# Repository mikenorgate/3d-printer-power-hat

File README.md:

# 3D Printer HAT

This 3D printer HAT is a PCB that allows you to connect your Raspberry PI to your 3D printer. The HAT (Hardware Attached on Top) sits on top of the Raspberry PI, allowing it to be powered by the printer's power supply. It also includes relays that allow the printer to be remotely turned on and off, making it easy to control your printer from your computer or mobile device.

## Board Features

- Step Down Voltage Converter: Converts the voltage supplied by your printer power supply unit (PSU) down to the 5 volts required by the Raspberry PI. This is an important safety feature, as using a higher voltage than the Raspberry PI is designed for can damage the board.
- Reverse Polarity Protection: Protects your Raspberry PI from damage in the event that the wiring is incorrectly connected. This can happen if you accidentally connect the positive and negative wires to the wrong pins on the HAT or the Raspberry PI.
- Backpower Protection: Will stop providing power to your PI via the HAT if you power it from a USB connection
- Printer Power Switch: Allows the power to the printer's main board to be remotely turned on and off. This is useful if you want to be able to start and stop your printer from your computer or mobile device.
- Auxiliary Power Switch: Can be used to power on and off an additional device, such as lights. This is useful if you want to be able to control other aspects of your printer setup from your computer or mobile device.
- PWM Fan Connector: Allows you to connect a pulse width modulation (PWM) fan to help keep the Raspberry PI cool. PWM fans are controlled by a signal from the Raspberry PI, which allows you to adjust their speed and therefore the amount of cooling they provide.

## Hardware Connection

To connect the HAT to your Raspberry PI and printer, you will need to follow the wiring diagram provided in the repository. This diagram shows you which pins on the HAT and the Raspberry PI need to be connected, as well as which wires from the printer's power supply need to be connected.

## Software

The HAT is compatible with the Klipper/Moonraker and Octoprint, which are open-source firmware and control software for 3D printers. Instructions for configuring these programs to work with the HAT are provided below.

### Klipper/Moonraker

To use the HAT with Klipper/Moonraker, you will need to add the following power configuration to your moonraker.conf file:

```yaml
[power printer]
type: gpio
pin: !gpiochip0/gpio17
initial_state: on
off_when_shutdown: True
off_when_shutdown_delay: 0
on_when_job_queued: True
locked_while_printing: True
restart_klipper_when_powered: True
restart_delay: 1.

[power aux]
type: gpio
pin: !gpiochip0/gpio27
initial_state: off
off_when_shutdown: True
off_when_shutdown_delay: 0
```

To avoid backpowering the printer via the USB port, we need to disable the ports when the power should be off. This can be achieved by using the `uhubctl` software, which is available at https://github.com/mvp/uhubctl.

To get started, SSH into your Raspberry PI and install uhubctl using the following command:

```bash
sudo apt install uhubctl
```

At the moment, Moonraker only supports controlling a small set of services. To get around this limitation, you can create a `MoonCord` service that can be used to control the USB ports. To do this, create a new file called MoonCord.service with the following content:

```
[Unit]
Description=USB Power

[Service]
ExecStart=sudo uhubctl -l 2 -a 1
ExecStop=sudo uhubctl -l 2 -a 0
RemainAfterExit=yes

[Install]
WantedBy=multi-user.target
```

Now add `bound_service: MoonCord` into the `power printer` section of the `moonraker.conf` file. This will cause the `MoonCord` service to be started and stopped along with the printer, allowing you to control the USB ports using the `uhubctl` software.

For more information about configuring Moonraker, see the documentation at https://moonraker.readthedocs.io/en/latest/configuration/.

### Octoprint

1. Install the PSU Control plugin by following the instructions at https://github.com/kantlivelong/OctoPrint-PSUControl.
2. Once the plugin is installed, you can access its settings by going to Settings > PSU Control in the Octoprint web interface.
3. In the plugin settings, enable the PSU Control feature and set the pin number for the printer power switch to 17 and the pin number for the auxiliary power switch to 27.
4. Save your changes and restart Octoprint.
5. Once Octoprint has restarted, you should be able to use the plugin to control the power to your printer and any other devices connected to the HAT. You can do this by going to the Control tab in the Octoprint web interface and clicking the on/off buttons for the printer and auxiliary power switches.

Note that this is just an example of how you might set up the HAT with Octoprint. The specific steps and settings may vary depending on your specific setup and requirements. For more detailed instructions, please refer to the documentation for the PSU Control plugin.

## Technical Specs

- Input Voltage: 4.5 V − 40 V
- Output Power: 5V DC / 3A
- Printer Output Max Current: 30A
- Aux Output Max Current: 10A

## Additional Content

The repository includes additional content that may be useful, including:

### Enclosures

- [Ender 3](enclosures/ender3)

### PCB

More information about the PCB and files required for manufacturing can be found [here](pcb)

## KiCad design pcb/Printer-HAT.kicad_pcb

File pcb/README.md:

## Manufacturing

IMPORTANT NOTE: Ensure the PCB thickness is no more than 1mm due to height constraints within the enclosure

### BOM

| Reference     | Value | Part Number         | LCSC    | Quantity |
| ------------- | ----- | ------------------- | ------- | -------- |
| C1            | 470uF | OGPE1601H471MF      | C269963 | 1        |
| C2            | 220uF | TAJD227K010RNJ      | C8024   | 1        |
| D1            |       | SS54                | C22452  | 1        |
| D3            |       | SK34                | C18895  | 1        |
| D4-D6         | Green | 19-217/GHC-YR1S2/3T | C72043  | 3        |
| D2,D7,D8      |       | 1N4148W             | C81598  | 3        |
| J1            |       | DB128V-5.0-3P-BK-S  | C424695 | 2        |
| J4            |       | B-2100S03P-A110     | C124376 | 1        |
| K1            |       | SRD-05VDC-SL-C      | C35449  | 1        |
| K2            |       | SLA-05VDC-SL-C      | C87367  | 1        |
| L1            | 47uH  | SLO1040H470MTT      | C182153 | 1        |
| P1            |       | C50982              | C50982  | 1        |
| Q1, Q2        |       | S8050               | C2146   | 2        |
| Q4            |       | DMMT5401-7-F        | C154733 | 1        |
| Q5            |       | DMG2305UX-7         | C150470 | 1        |
| R2            | 47K   | 0603WAF4702T5E      | C25819  | 1        |
| R3-R5, R8-R11 | 1K    | 0603WAF1001T5E      | C21190  | 7        |
| R1, R6, R7    | 10K   | 0603WAF1002T5E      | C25804  | 3        |
| U1            |       | LM2596S-5           | C347421 | 1        |
| U2, U3        |       | EL3H7               | C32565  | 2        |

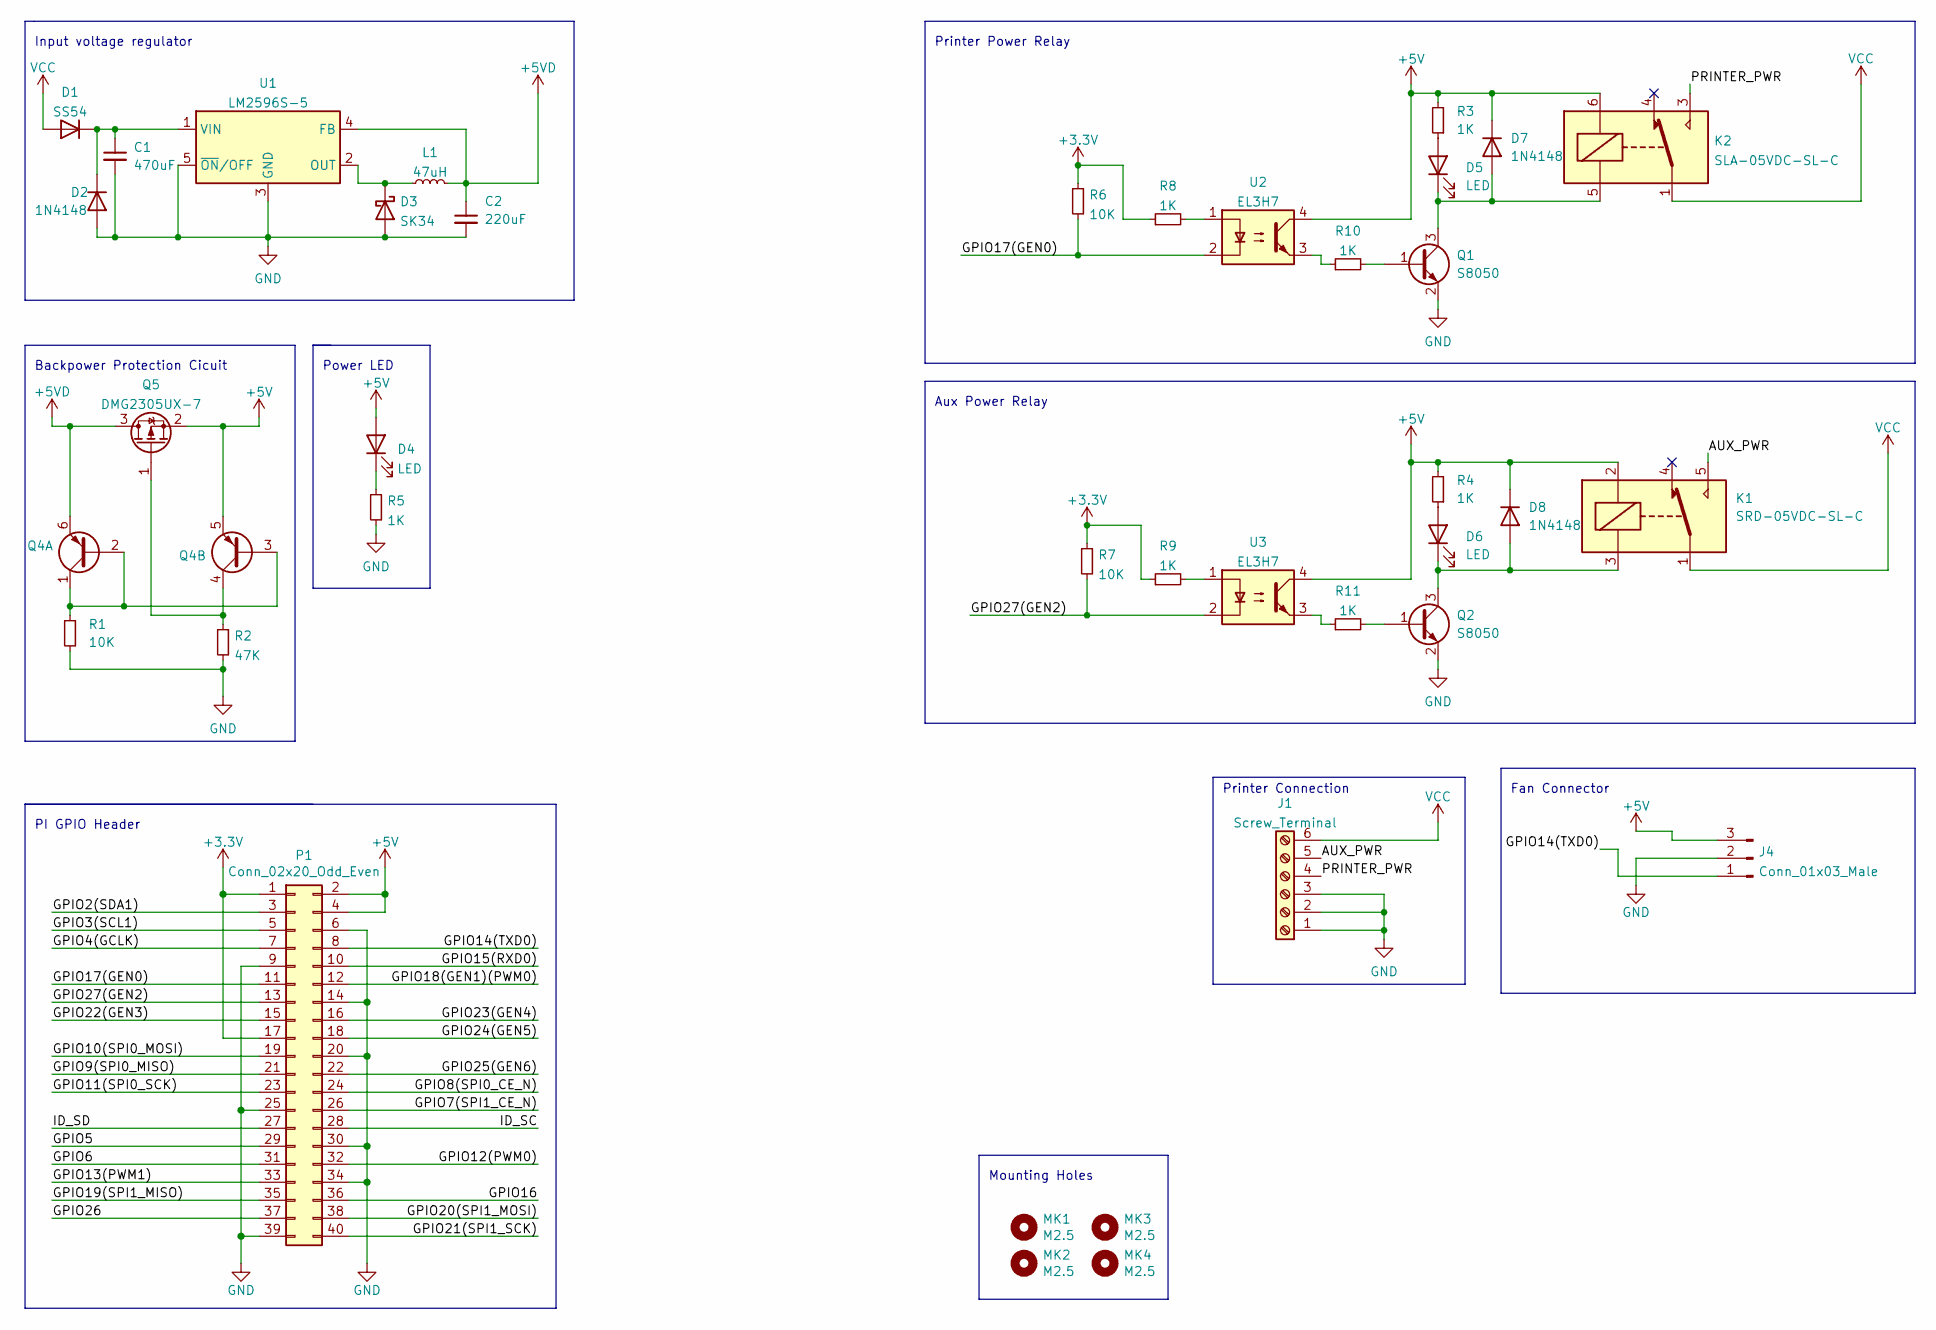
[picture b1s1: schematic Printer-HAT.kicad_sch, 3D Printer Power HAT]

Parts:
C1: 470uF; CP_Radial_D10.0mm_P5.00mm; Manufacturer_Part_Number OGPE1601H471MF; LCSC C269963
C2: 220uF; CP_EIA-7343-30_AVX-N; Manufacturer_Part_Number TAJD227K010RNJ; LCSC C8024
D1: SS54; D_MiniMELF; Manufacturer_Part_Number SS54; LCSC C22452
D2, D7, D8: 1N4148; D_MiniMELF; Manufacturer_Part_Number 1N4148W; LCSC C81598
D3: SK34; D_SMA; Manufacturer_Part_Number SK34; LCSC C18895
D4, D5, D6: LED; LED_0603_1608Metric; Manufacturer_Part_Number 19-217/GHC-YR1S2/3T; LCSC C72043
J1: Screw_Terminal; TerminalBlock_MetzConnect_Type011_RT05506HBWC_1x06_P5.00mm_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; Manufacturer_Part_Number WJ128V-5.0-6P; LCSC C192771
J4: Conn_01x03_Male; PinHeader_1x03_P2.54mm_Vertical; Manufacturer_Part_Number B-2100S03P-A110; LCSC C124376
K1: SRD-05VDC-SL-C; Manufacturer_Part_Number SRD-05VDC-SL-C; LCSC C35449
K2: SLA-05VDC-SL-C; SLA05VDCSLC; Manufacturer_Part_Number SLA-05VDC-SL-C; LCSC C87367
L1: 47uH; L_10.4x10.4_H4.8; Manufacturer_Part_Number SLO1040H470MTT; LCSC C182153
MK1, MK2, MK3, MK4: M2.5; MountingHole_2.7mm_M2.5_Pad
P1: Conn_02x20_Odd_Even; PinSocket_2x20_P2.54mm_Vertical; Manufacturer_Part_Number C50982; LCSC C50982
Q1, Q2: S8050; SOT-23; Manufacturer_Part_Number S8050 J3Y; JLCPCB_CORRECTION 0;0;180
Q4: Q_Dual_PNP_PNP_C1B1B2C2E2E1; SOT-23-6; Manufacturer_Part_Number DMMT5401-7-F; LCSC C154733
Q5: DMG2305UX-7; SOT-23; Manufacturer_Part_Number DMG2305UX-7; JLCPCB_CORRECTION 0;0;180
R1, R6, R7: 10K; R_0603_1608Metric; Manufacturer_Part_Number 0603WAF1002T5E; LCSC C25804
R2: 47K; R_0603_1608Metric; Manufacturer_Part_Number 0603WAF4702T5E; LCSC C25819
R3, R4, R5, R8, R9, R10, R11: 1K; R_0603_1608Metric; Manufacturer_Part_Number 0603WAF1001T5E; LCSC C21190
U1: LM2596S-5; TO-263-5_TabPin3; Manufacturer_Part_Number LM2596S-5.0; LCSC C347421
U2, U3: EL3H7; SOP-4_4.4x2.6mm_P1.27mm; Manufacturer_Part_Number EL3H7(B)(TA)-G; LCSC C32565

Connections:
+3V3: P1.1, P1.17, R6.1, R7.1, R8.1, R9.1
+5V: D4.2 (A), D7.1 (K), D8.1 (K), J4.3, K1.2, K2.6, P1.2, P1.4, Q4.5 (E2), Q5.2 (S), R3.2, R4.2, U2.4, U3.4
+5VD: C2.1, L1.2, Q4.6 (E1), Q5.3 (D), U1.4 (FB)
/AUX_PWR: J1.5, K1.5
/GPIO2(SDA1): P1.3
/GPIO3(SCL1): P1.5
/GPIO4(GCLK): P1.7
/GPIO5: P1.29
/GPIO6: P1.31
/GPIO7(SPI1_CE_N): P1.26
/GPIO8(SPI0_CE_N): P1.24
/GPIO9(SPI0_MISO): P1.21
/GPIO10(SPI0_MOSI): P1.19
/GPIO11(SPI0_SCK): P1.23
/GPIO12(PWM0): P1.32
/GPIO13(PWM1): P1.33
/GPIO14(TXD0): J4.1, P1.8
/GPIO15(RXD0): P1.10
/GPIO16: P1.36
/GPIO17(GEN0): P1.11, R6.2, U2.2
/GPIO18(GEN1)(PWM0): P1.12
/GPIO19(SPI1_MISO): P1.35
/GPIO20(SPI1_MOSI): P1.38
/GPIO21(SPI1_SCK): P1.40
/GPIO22(GEN3): P1.15
/GPIO23(GEN4): P1.16
/GPIO24(GEN5): P1.18
/GPIO25(GEN6): P1.22
/GPIO26: P1.37
/GPIO27(GEN2): P1.13, R7.2, U3.2
/ID_SC: P1.28
/ID_SD: P1.27
/PRINTER_PWR: J1.4, K2.3
GND: C1.2, C2.2, D2.2 (A), D3.2 (A), J1.1, J1.2, J1.3, J4.2, P1.6, P1.9, P1.14, P1.20, P1.25, P1.30, P1.34, P1.39, Q1.2 (E), Q2.2 (E), R1.2, R2.2, R5.2, U1.3 (GND), U1.5 (~ON/OFF)
unnamed: C1.1, D1.1 (K), D2.1 (K), U1.1 (VIN)
unnamed: D3.1 (K), L1.1, U1.2 (OUT)
unnamed: D4.1 (K), R5.1
unnamed: D5.2 (A), R3.1
unnamed: D6.2 (A), R4.1
unnamed: D6.1 (K), D8.2 (A), K1.3, Q2.3 (C)
unnamed: D5.1 (K), D7.2 (A), K2.5, Q1.3 (C)
unnamed: Q1.1 (B), R10.2
unnamed: Q2.1 (B), R11.2
unnamed: Q4.1 (C1), Q4.2 (B1), Q4.3 (B2), R1.1
unnamed: Q4.4 (C2), Q5.1 (G), R2.1
unnamed: R10.1, U2.3
unnamed: R11.1, U3.3
unnamed: R8.2, U2.1
unnamed: R9.2, U3.1
VCC: D1.2 (A), J1.6, K1.1, K2.1, K2.2

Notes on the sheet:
Power LED
Backpower Protection Cicuit
Input voltage regulator
Aux Power Relay
Printer Power Relay
Mounting Holes
Fan Connector
Printer Connection
PI GPIO Header

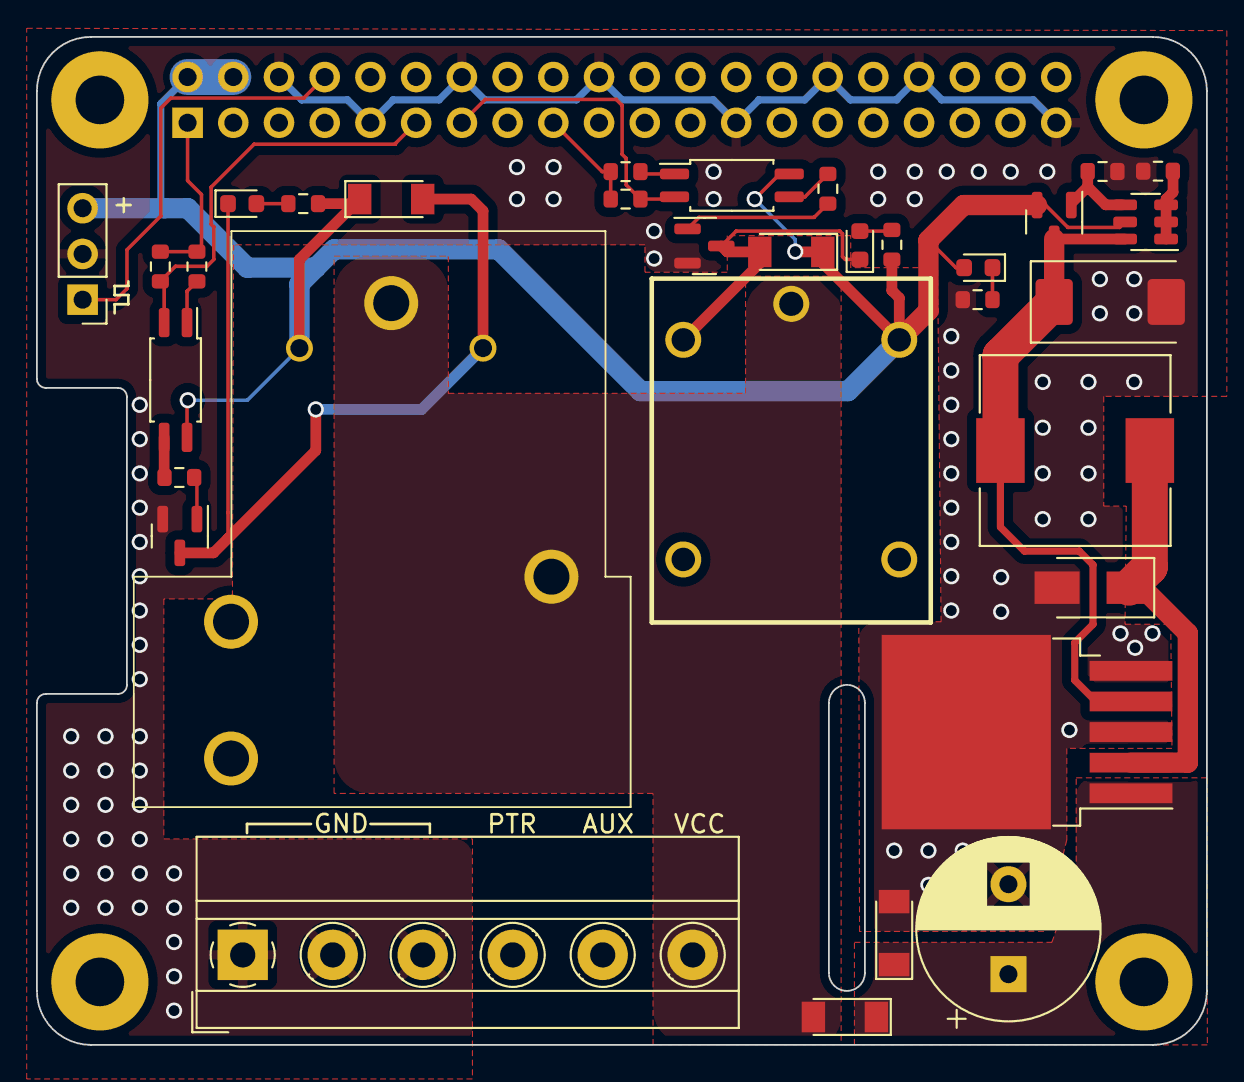
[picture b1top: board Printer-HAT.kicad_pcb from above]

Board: 2 copper layers, 65.0 x 56.0 mm, 38 parts (1 on the bottom side), 25 nets.

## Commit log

2022-01-25 update screw terminal to 5mm pitch
2022-01-30 enclosure start
2022-01-31 update enclosure
2022-02-20 add drawer and lid to enclosure
2022-02-20 reorganise
2022-02-20 add small tolerance to enclose lid
2022-02-20 cleanup silkscreen
2022-02-20 add tolerance to enclosure drawer
2022-02-26 fix issues with initial pcb
2022-02-26 fix PCB DRC errors
2022-03-02 readme template
2022-03-02 test
2022-03-02 update render
2022-03-03 add front view
2022-03-23 update docs
2022-03-23 more updates
2022-04-01 pcb docs
2022-04-01 enclosure
2022-04-01 crop
2022-04-01 Documentation
2022-12-06 readme improvements
